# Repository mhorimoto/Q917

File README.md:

# Q917
UECSシミュレータ

4chのアナログデータをUECSパケットにして送信する。

## H/W諸元

* CPU: Arduino UNO R3
* LAN: W5500
* LCD: 16x2

## UECS諸元

* UECS-ID: 10100C00000C
* MAC Address: 02:A2:73:0C:xx:xx

## Low core memory (EEPROM)

UECS-IDとMACアドレスを以下のアドレスに記録する．MSB first，Big endianにて記録す
る．

|  Address      | Data        |
|:-------------:|:------------|
| 00H〜05H      | UECS-ID     |
| 06H〜0BH      | MAC Address |
| 0CH〜1FH      | Reserved    |
| 20H〜7FFFH    | Data        |

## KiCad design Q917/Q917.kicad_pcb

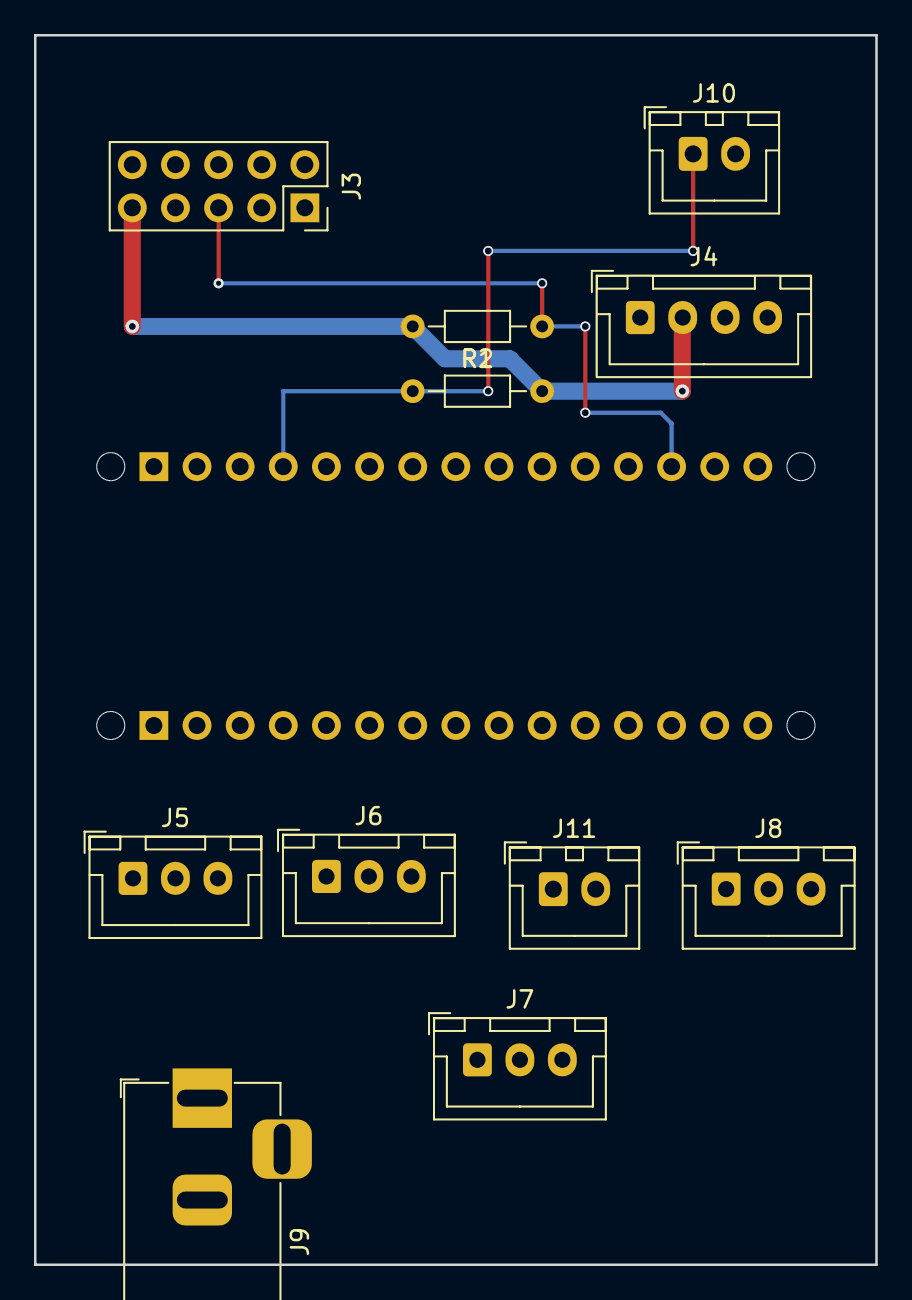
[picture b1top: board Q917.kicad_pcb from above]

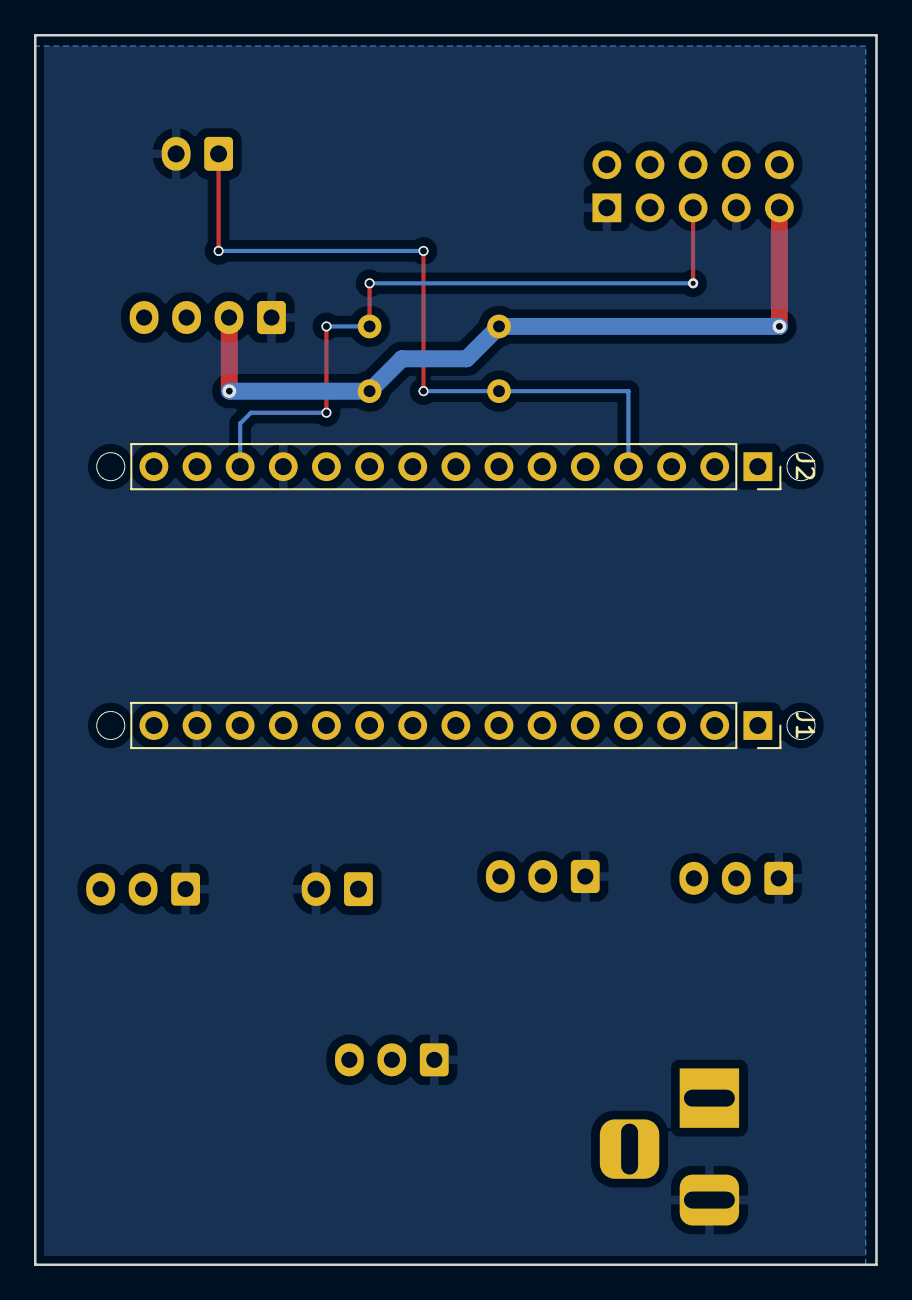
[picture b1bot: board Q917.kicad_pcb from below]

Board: 2 copper layers, 49.5 x 72.4 mm, 17 parts (2 on the bottom side), 14 nets.

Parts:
J1: Analog; PinSocket_1x15_P2.54mm_Vertical
J2: Digital; PinSocket_1x15_P2.54mm_Vertical
J3: to_W5500; PinSocket_2x05_P2.54mm_Vertical
J4: to_LCD; JST_XH_B4B-XH-A_1x04_P2.50mm_Vertical
J5: to_TEMP; JST_XH_B3B-XH-A_1x03_P2.50mm_Vertical
J6: to_HUMI; JST_XH_B3B-XH-A_1x03_P2.50mm_Vertical
J7: to_ILLU; JST_XH_B3B-XH-A_1x03_P2.50mm_Vertical
J8: to_ETC; JST_XH_B3B-XH-A_1x03_P2.50mm_Vertical
J9: DC5V; BarrelJack_Horizontal
J10: SELE; JST_XH_B2B-XH-A_1x02_P2.50mm_Vertical
J11: RESET; JST_XH_B2B-XH-A_1x02_P2.50mm_Vertical
MH1, MH2, MH3, MH4: MountingHole_65mil
R1, R2: 10k; R_Axial_DIN0204_L3.6mm_D1.6mm_P7.62mm_Horizontal

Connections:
+5V: J1.12, J3.9, J4.2, J5.3, J6.3, J7.3, J8.3, J9.1, R1.2, R2.2
/*D9: J2.4, J10.1, R2.1
/*D10/SS: J2.3, J3.4
/*D11/MOSI: J2.2, J3.6
/A0: J1.4, J5.2
/A1: J1.5, J6.2
/A2: J1.6, J7.2
/A3: J1.7, J8.2
/A4/SDA: J1.8, J4.3
/A5/SCL: J1.9, J4.4
/D12/MISO: J2.1, J3.8
/D13/SCK: J1.1, J3.2
/~RESET: J1.13, J2.13, J3.5, J11.1, R1.1
GND: J1.14, J2.12, J3.1, J3.7, J4.1, J5.1, J6.1, J7.1, J8.1, J9.2, J10.2, J11.2

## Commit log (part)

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2023-01-09 sche: ちょっと書いた
2023-01-10 sche: コネクタ類に変更
2023-01-10 sche: 初版完成
2023-01-10 sche: PCB配線開始
2023-01-14 docs: sche図をPDF更新
2023-01-16 prog: 書き始め
2023-01-16 prog: 予備的プログラム作成
2023-01-18 prog:少し追加
2023-01-31 prog: Ethernetを追記中
2023-12-26 リリース
2024-03-24 VRの文字盤を追加
2024-03-24 2024/3/28 セミナー対応
2024-03-24 セミナー用の設定完
2024-03-25 program completed
2024-09-23 KiCAD Version match
2024-10-31 KiCAD: 8.0.6
2024-11-25 ラベル作成
2025-01-15 UNO版はじめ
2025-01-15 ignore
2025-01-17 回路変更
2025-01-22 V2.10 表示位置の修正
2025-02-09 headerファイル作成
2025-05-21 KiCAD 8化
2025-08-01 2025年OpenCampus仕様
2025-08-03 OpenCampus2025
2025-12-02 回路図Ver合わせ，印刷
2025-12-02 写真更新
2025-12-02 Udp16528追加中
2026-04-14 CPU表記変更
2026-06-01 Add Photo
